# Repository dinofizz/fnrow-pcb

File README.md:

# FnRow

FnRow is a mechanical keyboard which features a single row of switches, in the form of a "function row". Each switch is configurable and can be programmed to perform as any key on a typical keyboard, or even combinations of key presses. FnRow is akin to a "macropad", but instead of having a square or rectangular "pad", the switches are stretched out in a single row.

See more details in my blog post about this project [here](https://www.dinofizzotti.com/blog/2021-02-07-fnrow-v1-a-configurable-function-row-layout-mechanical-keyboard/).

QMK firmware [here](https://github.com/dinofizz/qmk_firmware/tree/fnrow_v1/keyboards/dinofizz/fnrow/v1).

VIA layout file [here](https://github.com/dinofizz/keyboards/tree/fnrow_v1/src/dinofizz/fnrow).

# License

FnRow by Dino Fizzotti is licensed under [Attribution-ShareAlike 4.0 International](https://creativecommons.org/licenses/by-sa/4.0/)

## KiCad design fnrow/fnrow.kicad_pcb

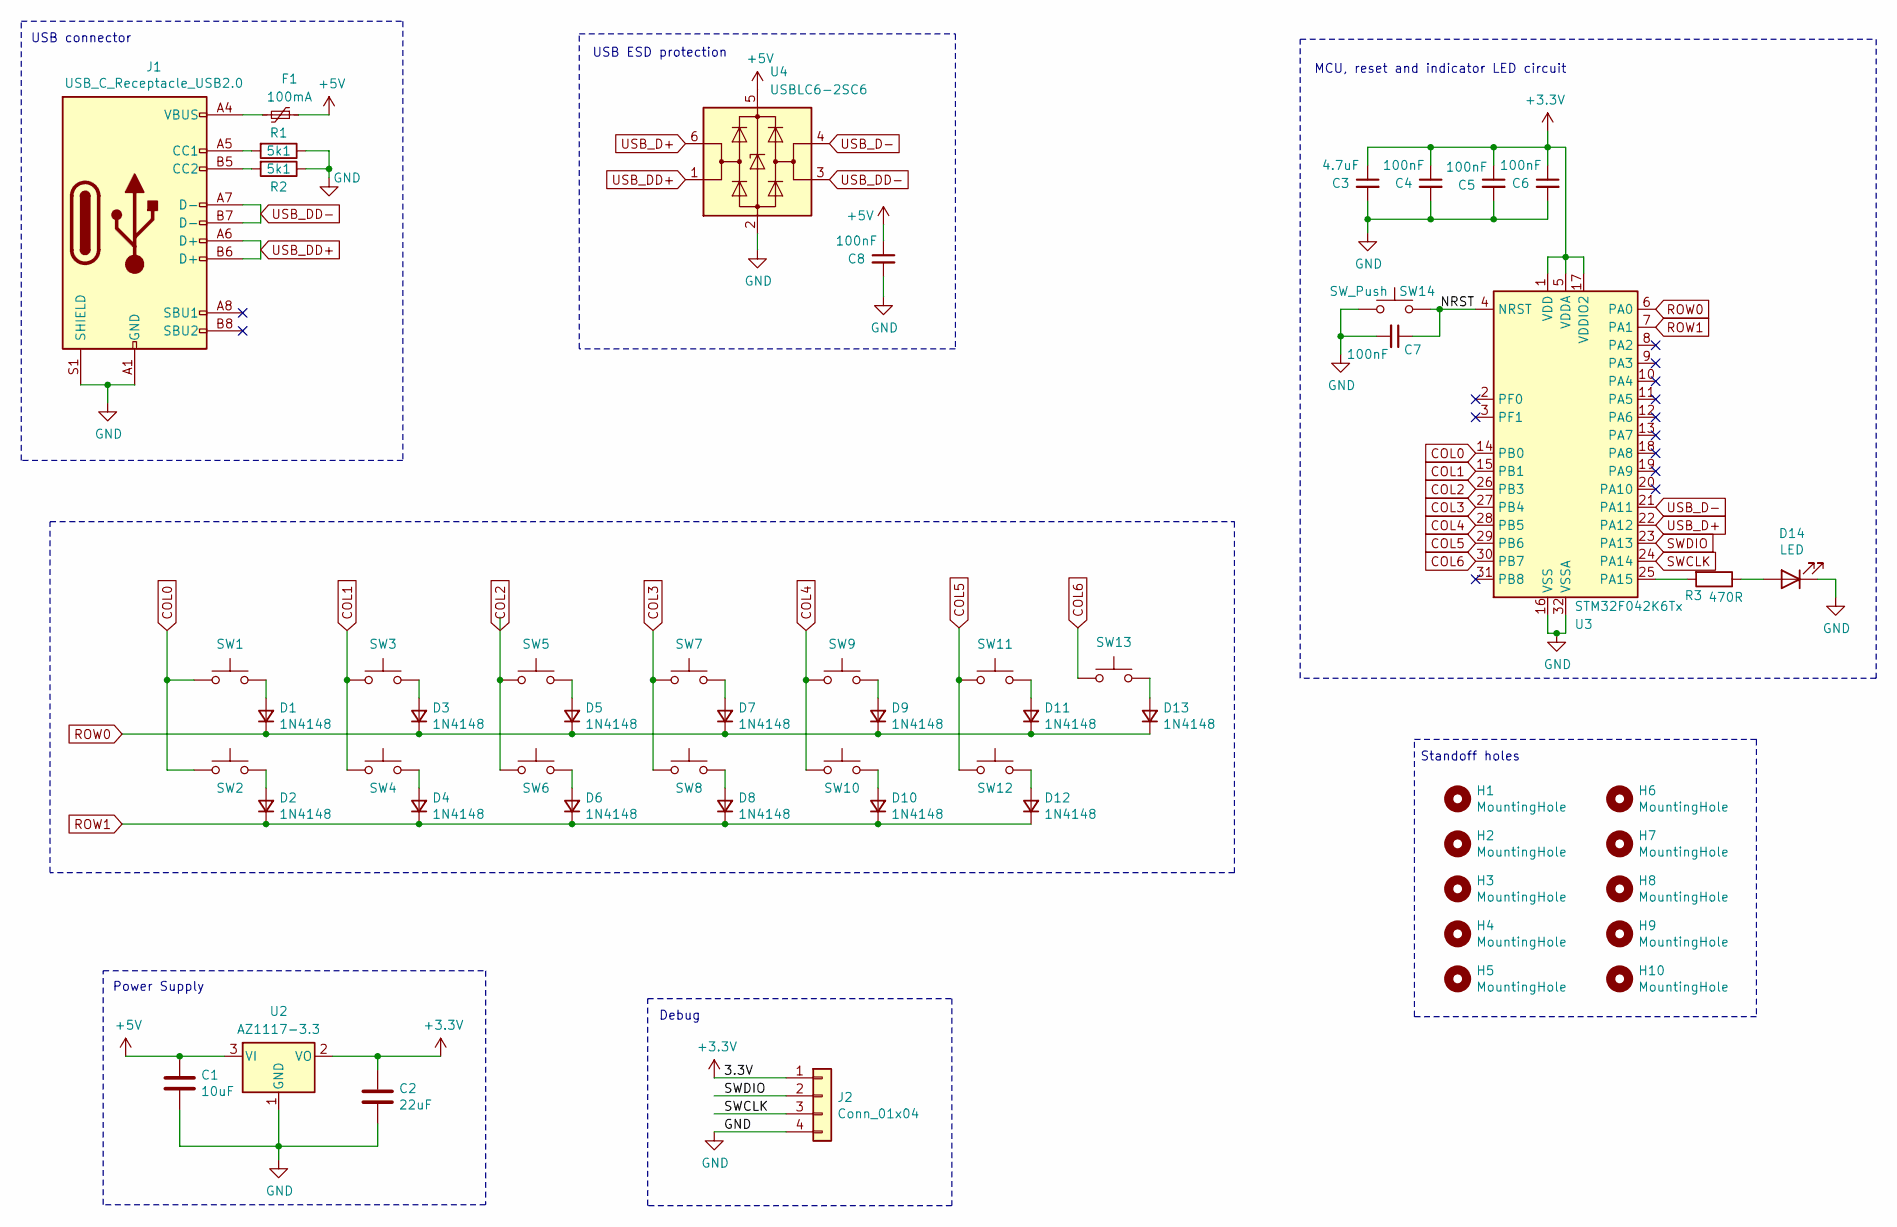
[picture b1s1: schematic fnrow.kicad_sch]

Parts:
C1: 10uF; C_0805_2012Metric
C2: 22uF; C_0805_2012Metric
C3: 4.7uF; C_0603_1608Metric
C4, C5, C6, C7, C8: 100nF; C_0402_1005Metric
D1, D2, D3, D4, D5, D6, D7, D8, D9, D10, D11, D12, D13: 1N4148; D_SOD-123
D14: LED; LED_0805_2012Metric
F1: 100mA; Fuse_0805_2012Metric; LCSC C2687880
H1, H2, H3, H4, H5, H6, H7, H8, H9, H10: MountingHole; MountingHole_3.2mm_M3
J1: USB_C_Receptacle_USB2.0; USB_C_Receptacle_HRO_TYPE-C-31-M-12; LCSC C2689845
J2: Conn_01x04; PinHeader_1x04_P2.54mm_Horizontal
R1, R2: 5k1; C_0402_1005Metric
R3: 470R; C_0402_1005Metric
SW1, SW2, SW3, SW4, SW5, SW6, SW7, SW8, SW9, SW10, SW11, SW12, SW13: SW_Push; SW_Cherry_MX_1.00u_PCB
SW14: SW_Push; SW_Push_1P1T_XKB_TS-1187A; LCSC C318884
U2: AZ1117-3.3; SOT-223; LCSC C92102
U3: STM32F042K6Tx; LQFP-32_7x7mm_P0.8mm; LCSC C69216
U4: USBLC6-2SC6; SOT-23-6; LCSC C2827654

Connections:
+3V3: C2.1, C3.1, C4.1, C5.1, C6.1, J2.1, U2.2 (VO), U3.1 (VDD), U3.5 (VDDA), U3.17 (VDDIO2)
+5V: C1.1, C8.1, F1.1, U2.3 (VI), U4.5 (VBUS)
/NRST: C7.1, SW14.2, U3.4 (NRST)
COL0: SW1.2, SW2.2, U3.14 (PB0)
COL1: SW3.2, SW4.2, U3.15 (PB1)
COL2: SW5.2, SW6.2, U3.26 (PB3)
COL3: SW7.2, SW8.2, U3.27 (PB4)
COL4: SW9.2, SW10.2, U3.28 (PB5)
COL5: SW11.2, SW12.2, U3.29 (PB6)
COL6: SW13.2, U3.30 (PB7)
GND: C1.2, C2.2, C3.2, C4.2, C5.2, C6.2, C7.2, C8.2, D14.1 (K), J1.A1 (GND), J1.A12 (GND), J1.B1 (GND), J1.B12 (GND), J1.S1 (SHIELD), J2.4, R1.1, R2.1, SW14.1, U2.1 (GND), U3.16 (VSS), U3.32 (VSSA), U4.2 (GND)
unnamed: D1.2 (A), SW1.1
unnamed: D2.2 (A), SW2.1
unnamed: D3.2 (A), SW3.1
unnamed: D4.2 (A), SW4.1
unnamed: D5.2 (A), SW5.1
unnamed: D6.2 (A), SW6.1
unnamed: D7.2 (A), SW7.1
unnamed: D8.2 (A), SW8.1
unnamed: D9.2 (A), SW9.1
unnamed: D10.2 (A), SW10.1
unnamed: D11.2 (A), SW11.1
unnamed: D12.2 (A), SW12.1
unnamed: D13.2 (A), SW13.1
unnamed: D14.2 (A), R3.1
unnamed: F1.2, J1.A4 (VBUS), J1.A9 (VBUS), J1.B4 (VBUS), J1.B9 (VBUS)
unnamed: J1.A5 (CC1), R1.2
unnamed: J1.B5 (CC2), R2.2
unnamed: R3.2, U3.25 (PA15)
ROW0: D1.1 (K), D3.1 (K), D5.1 (K), D7.1 (K), D9.1 (K), D11.1 (K), D13.1 (K), U3.6 (PA0)
ROW1: D2.1 (K), D4.1 (K), D6.1 (K), D8.1 (K), D10.1 (K), D12.1 (K), U3.7 (PA1)
SWCLK: J2.3, U3.24 (PA14)
SWDIO: J2.2, U3.23 (PA13)
USB_D+: U3.22 (PA12), U4.6 (I/O1)
USB_D-: U3.21 (PA11), U4.4 (I/O2)
USB_DD+: J1.A6 (D+), J1.B6 (D+), U4.1 (I/O1)
USB_DD-: J1.A7 (D-), J1.B7 (D-), U4.3 (I/O2)

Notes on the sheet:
Power Supply
USB ESD protection
Debug
Standoff holes
USB connector
MCU, reset and indicator LED circuit

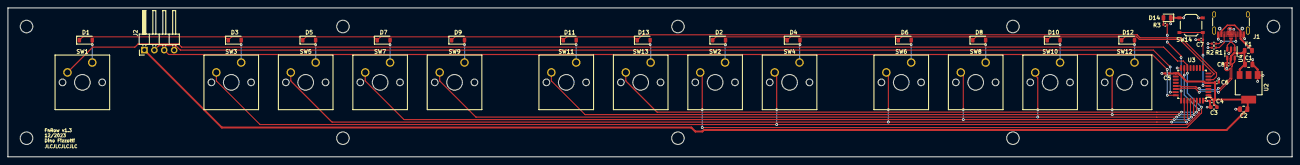
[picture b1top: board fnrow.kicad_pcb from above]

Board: 2 copper layers, 328.6 x 38.1 mm, 55 parts (0 on the bottom side), 37 nets.

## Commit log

2021-02-07 Improving license text with link to license
2021-02-07 Adding blog post URL
2023-12-28 v1.2 changes
2023-12-29 Adding files
